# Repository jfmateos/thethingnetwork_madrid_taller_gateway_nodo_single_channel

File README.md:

# Taller TTNMadrid

- Gateway Mono-canal
  - Si no es capaz de compilarlo con Arduino, pruebe a degradar el gestor de placas ESP8266 a la versión 2.4.2
  - Modelos 3D para la carcasa (sólo piezas amarillas): https://www.tinkercad.com/things/hQr2E4W4Zfp
- Nodo Puerta Abierta
  - Modelos 3D para la carcasa (sólo piezas amarillas): https://www.tinkercad.com/things/ilqWqOo9zD4

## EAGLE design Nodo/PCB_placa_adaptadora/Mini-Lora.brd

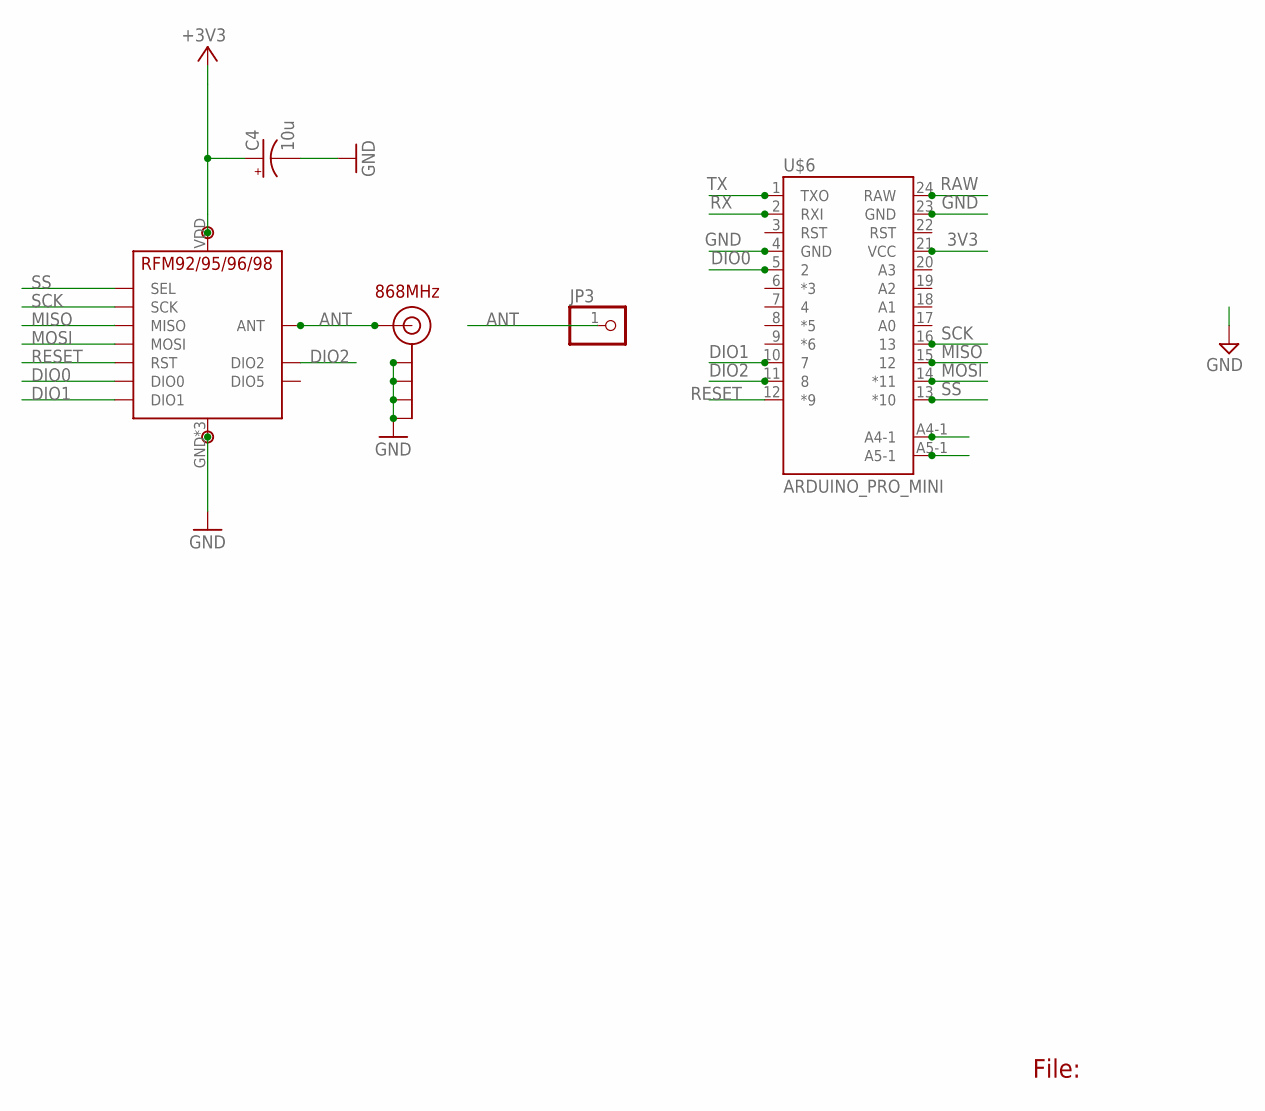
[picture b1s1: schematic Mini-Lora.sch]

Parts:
C4: 10u; CPOL-RADIAL-10UF-25V
J$2: ANTENNATINY; SMA_UFL_PAD_TINY
JP3: PINHD-1X1; 1X01
P1: GND; PAD
P2: 3v3; PAD
U$5: RFM95
U$6: ARDUINO_PRO_MINI

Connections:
3V3: C4.1 (+), P2.1, U$5.VDD (VCC), U$6.21 (VCC)
ANT: J$2.ANT1 (SIGNAL), J$2.ANT2 (SIGNAL), J$2.ANT3 (SIGNAL), JP3.1, U$5.ANT
DIO0: U$5.DIO0, U$6.5 (2)
DIO1: U$5.DIO1, U$6.10 (7)
DIO2: U$5.DIO2, U$6.11 (8)
GND: C4.2 (-), J$2.GND1 (GND), J$2.GND2 (GND), J$2.GND3 (GND), J$2.GND4 (GND), P1.1, U$5.GND, U$5.GND1 (GND), U$5.GND2 (GND), U$6.4 (GND), U$6.23 (GND)
MISO: U$5.MISO, U$6.15 (12)
MOSI: U$5.MOSI, U$6.14 (*11)
RAW: U$6.24 (RAW)
RESET: U$5.RST, U$6.12 (*9)
RX: U$6.2 (RXI)
SCK: U$5.SCK, U$6.16 (13)
SCL: U$6.A5-1
SDA: U$6.A4-1
SS: U$5.NSS (SEL), U$6.13 (*10)
TX: U$6.1 (TXO)

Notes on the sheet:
File:
868MHz

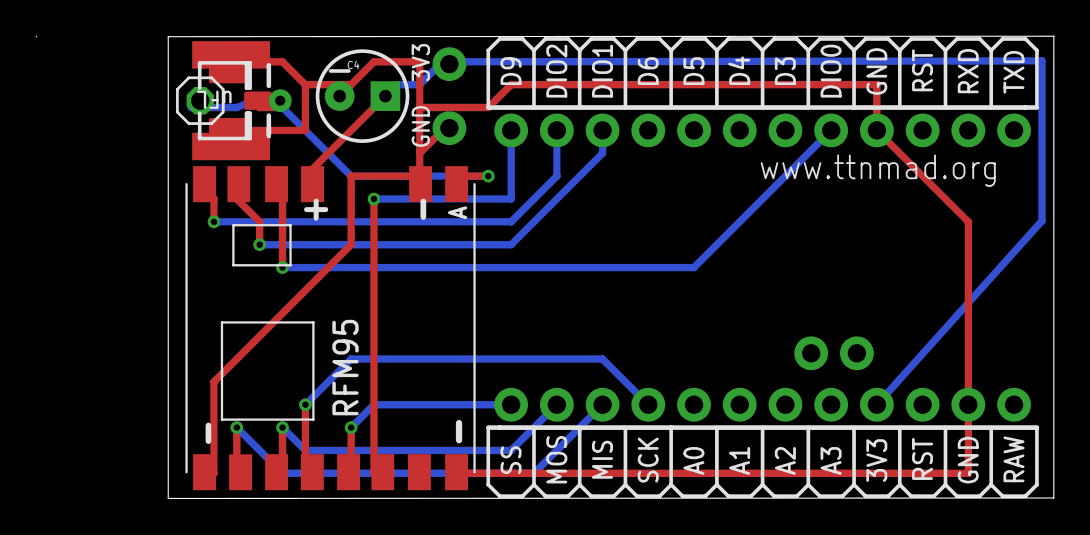
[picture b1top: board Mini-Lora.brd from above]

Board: 2 copper layers, 49.2 x 25.7 mm, 7 parts (0 on the bottom side), 11 nets.

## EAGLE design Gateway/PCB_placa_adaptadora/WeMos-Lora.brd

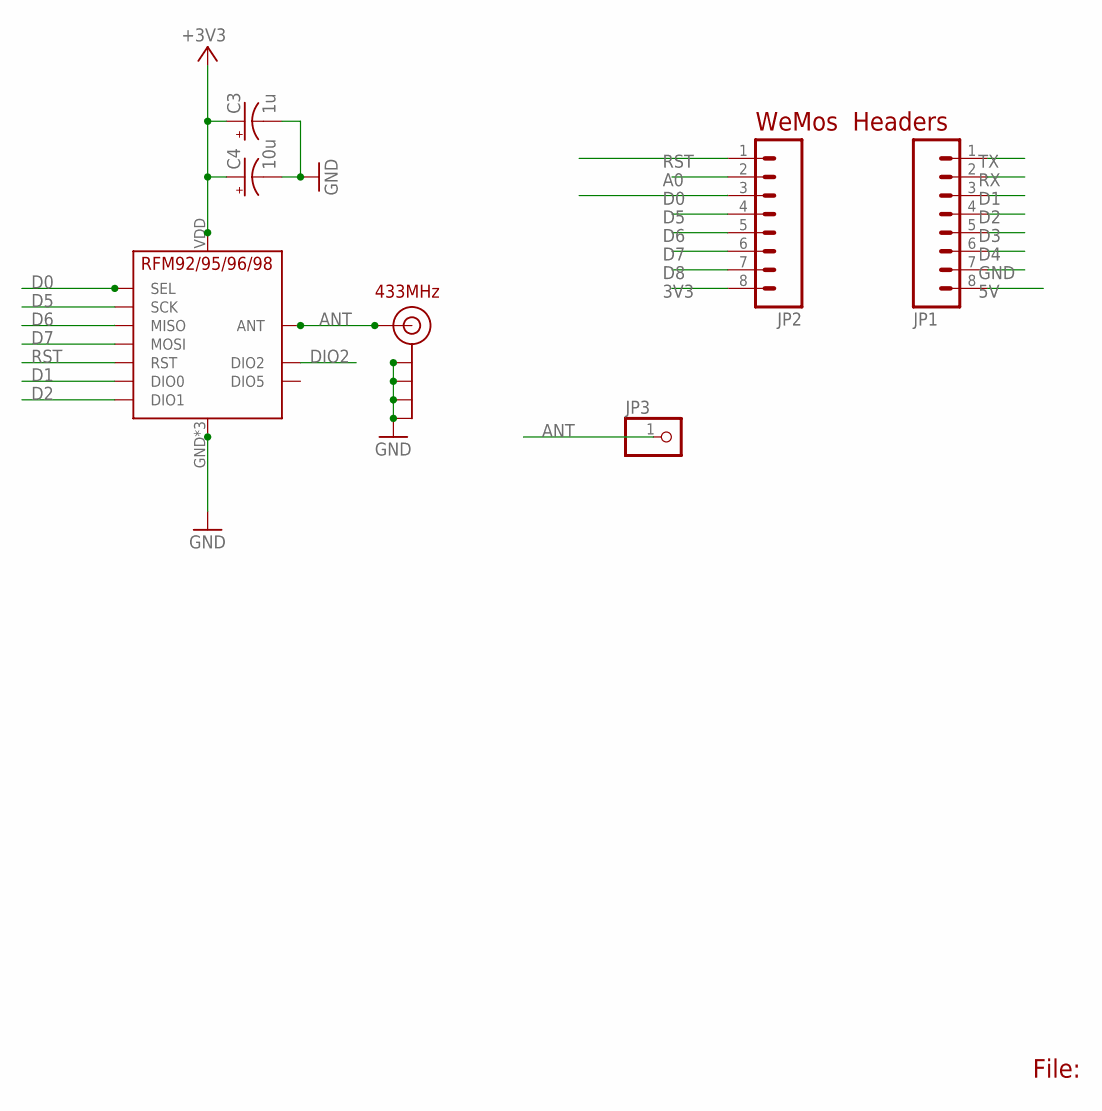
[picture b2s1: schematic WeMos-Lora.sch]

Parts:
C3: 1u; CPOL-RADIAL-10UF-25V
C4: 10u; CPOL-RADIAL-10UF-25V
J$2: ANTENNATINY; SMA_UFL_PAD_TINY
JP1, JP2: M08NO_SILK_FEMALE_PTH; 1X08_NO_SILK
JP3: PINHD-1X1; 1X01
U$5: RFM95

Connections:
3V3: C3.1 (+), C4.1 (+), JP2.8, U$5.VDD (VCC)
5V: JP1.8
A0: JP2.2
ANT: J$2.ANT1 (SIGNAL), J$2.ANT2 (SIGNAL), J$2.ANT3 (SIGNAL), JP3.1, U$5.ANT
D0: JP2.3, U$5.NSS (SEL)
D1: JP1.3, U$5.DIO0
D2: JP1.4, U$5.DIO1
D3: JP1.5
D4: JP1.6
D5: JP2.4, U$5.SCK
D6: JP2.5, U$5.MISO
D7: JP2.6, U$5.MOSI
D8: JP2.7
DIO2: U$5.DIO2
GND: C3.2 (-), C4.2 (-), J$2.GND1 (GND), J$2.GND2 (GND), J$2.GND3 (GND), J$2.GND4 (GND), JP1.7, U$5.GND, U$5.GND1 (GND), U$5.GND2 (GND)
RST: JP2.1, U$5.RST
RX: JP1.2
TX: JP1.1

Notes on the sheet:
File:
WeMos Headers
433MHz

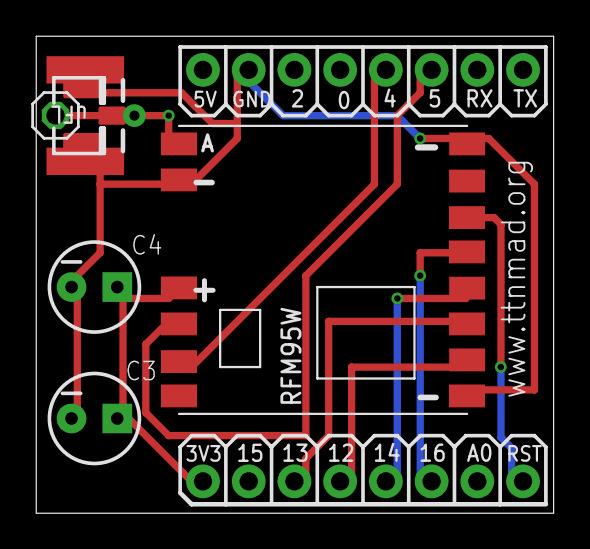
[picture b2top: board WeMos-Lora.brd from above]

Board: 2 copper layers, 28.7 x 26.5 mm, 7 parts (0 on the bottom side), 10 nets.

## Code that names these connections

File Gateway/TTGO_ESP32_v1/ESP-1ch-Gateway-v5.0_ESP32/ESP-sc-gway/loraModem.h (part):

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#define NUM_HOPS 3

bool _cad= (bool) _CAD;	// Set to true for Channel Activity Detection, only when dio 1 connected
bool _hop=false;		// experimental; frequency hopping. Only use when dio2 connected
bool inHop=false;
unsigned long nowTime=0;
unsigned long hopTime=0;
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#if _PIN_OUT==1
// Definition of the GPIO pins used by the Gateway for Hallard type boards
struct pins {
	uint8_t dio0=15;	// GPIO15 / D8. For the Hallard board shared between DIO0/DIO1/DIO2
	uint8_t dio1=15;	// GPIO15 / D8. Used for CAD, may or not be shared with DIO0
	uint8_t dio2=15;	// GPIO15 / D8. Used for frequency hopping, don't care
	uint8_t ss=16;		// GPIO16 / D0. Select pin connected to GPIO16 / D0
	uint8_t rst=0;		// GPIO0 / D3. Reset pin not used	
	// MISO 12 / D6
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#elif _PIN_OUT==2
// For ComResult gateway PCB use the following settings
struct pins {
	uint8_t dio0=5;		// GPIO5 / D1. Dio0 used for one frequency and one SF
	uint8_t dio1=4;		// GPIO4 / D2. Used for CAD, may or not be shared with DIO0
	uint8_t dio2=0;		// GPIO0 / D3. Used for frequency hopping, don't care
	uint8_t ss=15;		// GPIO15 / D8. Select pin connected to GPIO15
	uint8_t rst=0;		// GPIO0 / D3. Reset pin not used	
} pins;
#elif _PIN_OUT==3
// For ComResult gateway PCB use the following settings
struct pins {
  uint8_t dio0=26;   // GPIO5 / D1. Dio0 used for one frequency and one SF
  uint8_t dio1=33;   // GPIO4 / D2. Used for CAD, may or not be shared with DIO0
  uint8_t dio2=32;   // GPIO0 / D3. Used for frequency hopping, don't care
  uint8_t ss=18;    // GPIO15 / D8. Select pin connected to GPIO15
  uint8_t rst=14;    // GPIO0 / D3. Reset pin not used 
// Pin definetion of WIFI LoRa 32
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#define MOSI    27   // GPIO27 -- SX127x's MOSI
#define SS      18   // GPIO18 -- SX127x's CS
#define RST     14   // GPIO14 -- SX127x's RESET
#define DIO0    26   // GPIO26 -- SX127x's IRQ(Interrupt Request)  
} pins;
#else
	// Use your own pin definitions, and uncomment #error line below
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
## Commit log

2018-04-09 Inicio del repositorios
2018-04-13 Corrección nombres archivos nodo
2018-04-13 Añadido BOM
2018-05-04 Cambio orden diapositivas presentación
2018-05-07 Añado programa para ttnmapper
2018-05-17 Corrección el el board de la placa del nodo
    Bug detectado por @giltesa
2018-05-24 Añadir versión de nodo y gateway con placa TTGO ESP32 v1
2018-06-06 Separar datos privados del código principal
2018-06-06 Corregir información en pantalla
2018-06-06 Separar información privada
2018-06-06 Quitar líneas innecesarias
2018-06-06 Git Ignore
2018-06-06 Resetear frecuencias después del JOIN
2018-06-09 Library implementation. WIP
2018-06-09 Copiar claves al inicio
2018-06-10 Librería Nodo OTAA funcinando :)
2018-06-10 Añadir manejador para datos recibidos
2018-06-10 Integrar datos recibidos en código principal
2018-06-11 Reservar memoria
2018-11-30 Añade librerias para el Nodo
2018-12-02 Show Gateway IP address in Serial monitor
2018-12-02 Add sketch configs for Visual Studio Code
2018-12-12 Ejemplo de prueba para el nodo TTN_MAD V3
2018-12-14 Add ttnmapper sketch
2018-12-14 Add ttnmapper_node/Readme.md
2018-12-15 Fix errata en ttnmapper/Readme.md
2018-12-15 Add env install script for CI
2018-12-15 Add Travis-CI configuration
2018-12-15 Add safelist to travis ci conf
2018-12-15 Adjust travis ci conf
2018-12-15 CI: change for install_env script
2018-12-15 Only install boards if not cached
2018-12-15 Add missing Nodo/ttnmapper_node/Makefile
2018-12-15 Only clone arduino-mk if not cached
2018-12-15 Fix paths in Makefile
2018-12-15 Add all libraries for Nodos
2018-12-15 Fix another path in makefile
2018-12-15 Remove CI branch safelist
2018-12-15 Fix CI build
    Squashed commit of the following:
    commit 431ab641cf7f0a189509dd222ec261d6abe55dc7
    Author: Alexandre Dumont <adumont@gmail.com>
    Date: Sat Dec 15 17:31:37 2018 +0100
    Remove CI branch safelist
    commit 42cf2ed70c23d42d99ec28e7eb64ed590557796c
2018-12-15 Fix CI build (for real!)
    Squashed commit of the following:
    commit cce6213fdec5fca77a3815445da5fb2a67f56a46
    Author: Alexandre Dumont <adumont@gmail.com>
    Date: Sat Dec 15 20:38:45 2018 +0100
    Fix CI build?
    commit 5727e97c468c8e747af74e802c8f1859c21a8088
2018-12-16 Better paths for CI env
    Squashed commit of the following:
    commit 40fc772d202ae8699fe378a7153bc96550145f74
    Author: Alexandre Dumont <adumont@gmail.com>
    Date: Sun Dec 16 18:16:48 2018 +0100
    cd back to source folder
    commit 304d18cd07b1ed9c9db25c31b185a349772ed233
2018-12-16 Build Nodo Puerta Abierta (CI)
2018-12-17 CI: build Gateway
2018-12-18 Replace arduino-mk with arduino-builder
    Fixup path in Makefile
2018-12-18 CI less verbose builds
2018-12-18 Introduce a common Arduino.mk
2018-12-18 Remove warnings in arduino builds

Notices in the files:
Gateway/TTGO_ESP32_v1/ESP-1ch-Gateway-v5.0_ESP32/ESP-sc-gway/loraModem.h:
Copyright (c) 2016, 2017 Maarten Westenberg version for ESP8266
All rights reserved. This program and the accompanying materials
are made available under the terms of the MIT License
parts and their libraries:
SparkFun-Connectors: Licensing: Creative Commons ShareAlike 4.0 International - https://creativecommons.org/licenses/by-sa/4.0
